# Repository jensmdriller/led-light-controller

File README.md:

# led-light-controller
This repo focuses around the development of an arduino based controller to program and control LED strip lights. 

- - - -

**Note**, I've created this repo to serve as a centralized storage for all of the LED project files. I'll update the README file as the project progresses. The README as well as the files contained within this folder should be a good reference for any future development. 

- - - -
### Overview
The components used herein are widely used in the hacker/maker community. Thus, much of the work has already been done for us. 
- For example, the **Atmel SAMD21** microcontroller is found in the Arduino Zero as well as many other developer boards.
- The lights are essentially a SMD 5050 LED with an integrated WS2811 microcontroller.
  - This integration of LED + MCU is referred to as **WS2812B**, but companies such as Adafruit use WS2812B LEDs and rebrand it as Neopixels. Other companies are starting to do the same. 
- The main hurdle of using WS2812B chips is their 5v operating voltage as well as their higher current draw. This prevents long runs without power injection along the way

- - - -

### Phase 1: Hardware Design
- Determining which microcontroller (MCU) and WiFi module to use
- Finalize schematic (including audio in or microphone)
- Configuring the power supplies
- Laying out the circuit board
- Ordering the circuit board and components
- Soldering/Assembling the first prototypes

### Phase 2: Coding - App & Embedded Software Design:
- Learn how the microcontroller (MCU) communicates with the LEDs
- Develop initial programs/sequences to control lights
- Work on WiFi integration
- App development (Android & IOS)
- Configure sync between app and LED controller via WiFI
- Refine app and implement additional functionality 

### Phase 3: Case/Enclosure Design
- Well let’s cross this bridge when we come to it

- - - -
- - - -

### Coming to Terms With Reality
- No one is going to buy this. This work is purely out of interest and enjoyment
- Good WiFi chipsets are protected by NDA. Thus we have to use more expensive and more discrete chipsets
- There already exists a lot of products on the market that have done exactly this - well almost...
- I'm pretty busy these days, so progress might be slow

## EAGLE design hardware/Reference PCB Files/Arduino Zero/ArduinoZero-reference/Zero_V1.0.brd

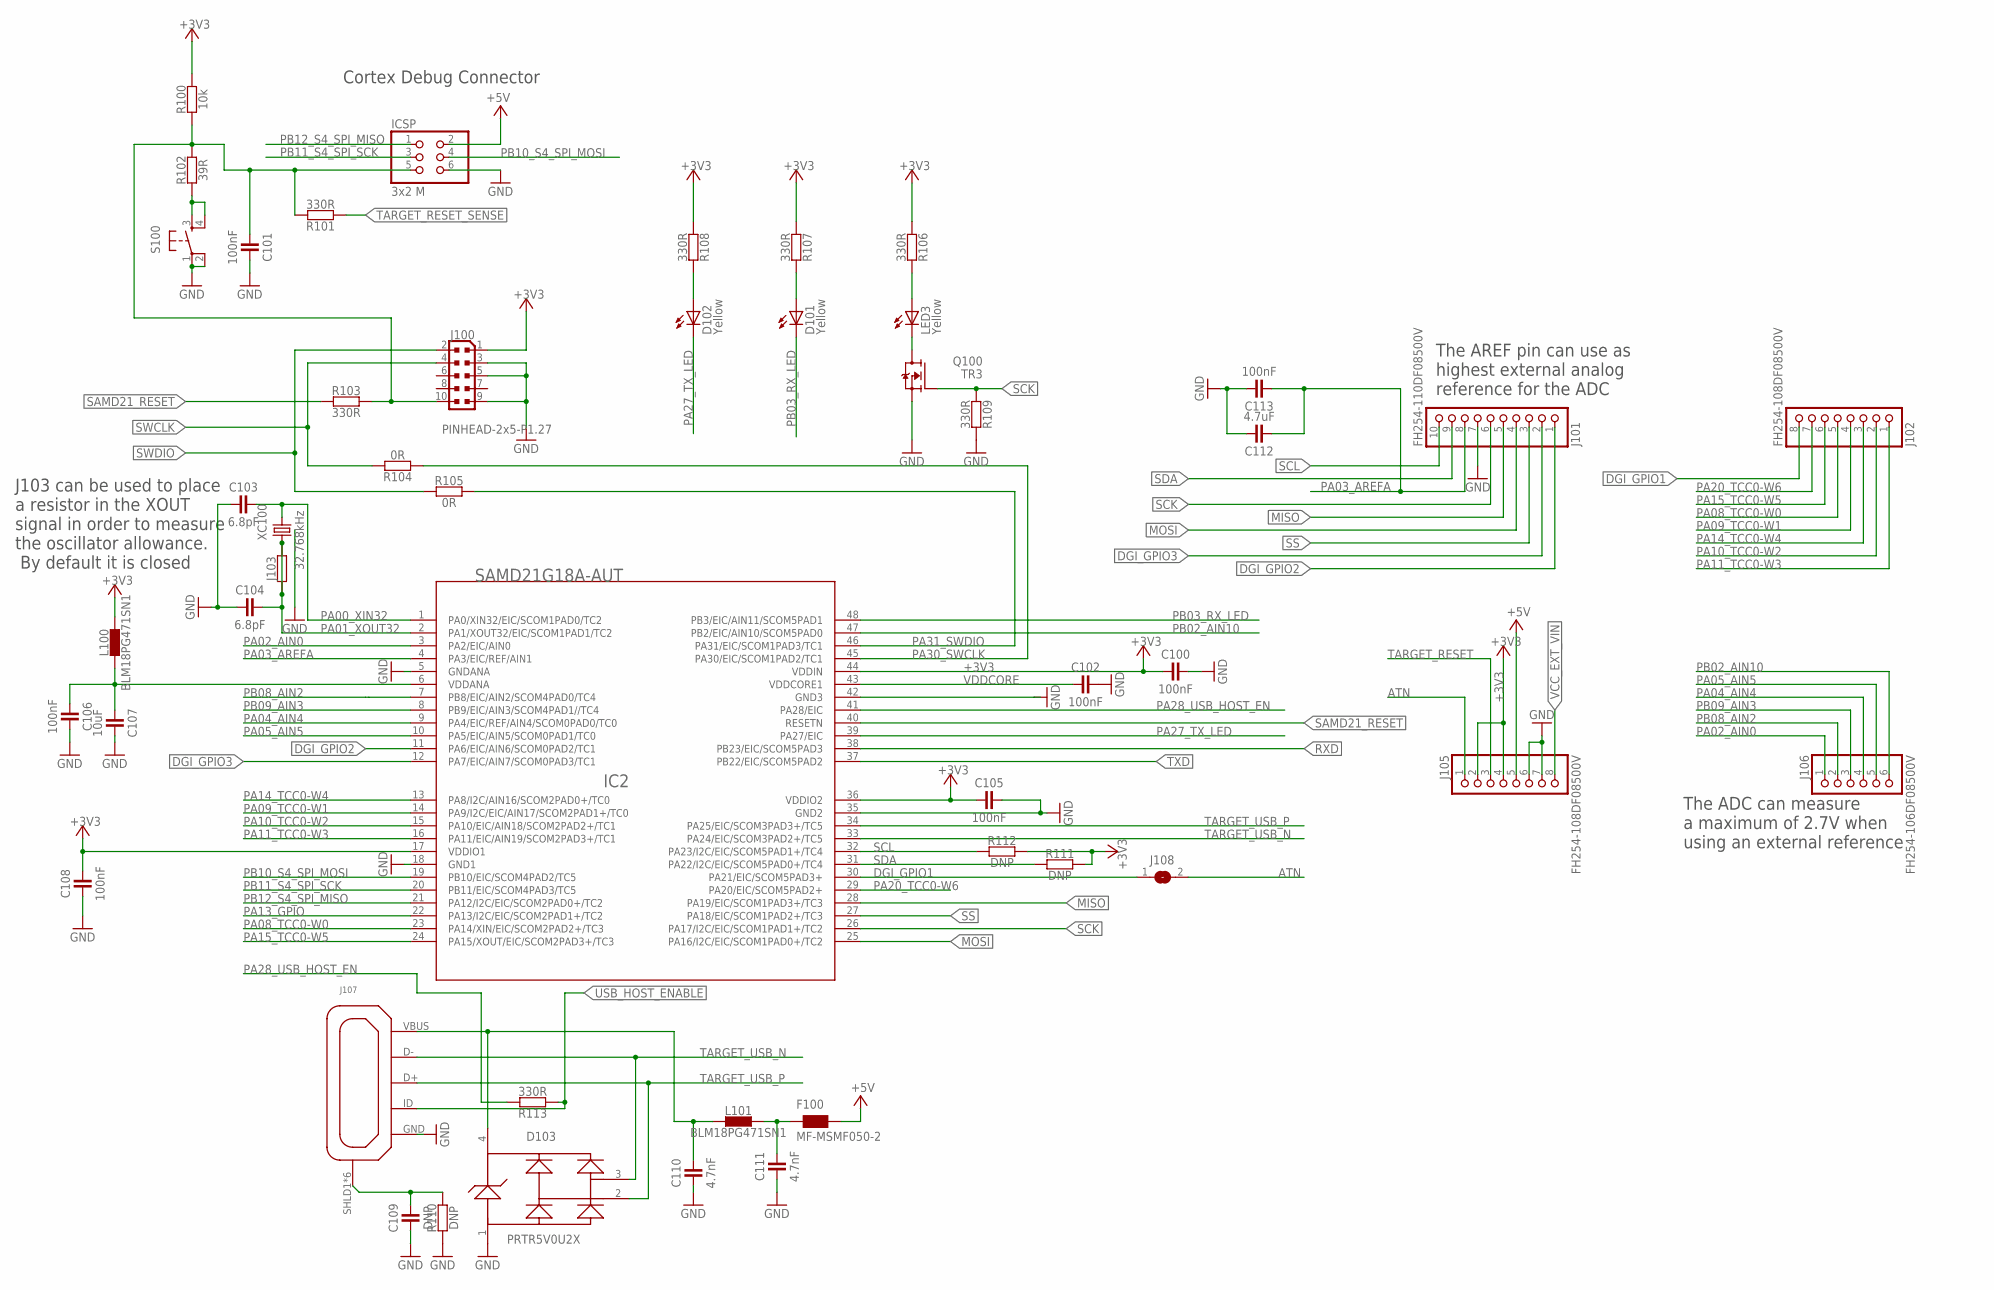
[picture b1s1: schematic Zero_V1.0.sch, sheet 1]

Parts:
C100, C101, C102, C105, C106, C108, C113: 100nF; C0402
C103, C104: 6.8pF; C0402
C107: 10uF; C0603
C109: DNP; C0402
C110, C111: 4.7nF; C0402
C112: 4.7uF; C0603
D101, D102: Yellow; CHIPLED_0805
D103: PRTR5V0U2XB; SOT143B
F100: MF-MSMF050-2; WUERTH-ELEKTRONIK_1812
IC2: SAMD21G18A-AUT; TQFP48
ICSP: 3x2 M; 2X03
J100: PINHEAD-2x5-P1.27; PINHEAD_2X05_127
J101: FH254-110DF08500V; 1X10
J102, J105: FH254-108DF08500V; 1X08
J103: RESISTORS-0402; C0402
J106: FH254-106DF08500V; 1X06
J107: ZX62-AB-5PA; USB-MICRO-10103594
J108: SJ
L100, L101: BLM18PG471SN1; C0603
LED3: Yellow; CHIPLED_0805
R100: 10k; C0402
R101, R103, R106, R107, R108, R109, R113: 330R; C0402
R102: 39R; C0402
R104, R105: 0R; C0402
R110, R111, R112: DNP; C0402
S100: PUSHBUTTON3; TS42_4PINS
TR3: Q100; SOT-23
XC100: 32.768kHz; CRYSTAL_TC26SMD

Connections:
+3V3: C100.1, C105.1, C108.2, IC2.17 (VDDIO1), IC2.36 (VDDIO2), IC2.44 (VDDIN), J100.1, J105.2, J105.4, L100.2, R100.2, R106.1, R107.1, R108.1, R111.2, R112.2; also elsewhere on the board
+5V: F100.2, ICSP.2, J105.5; also elsewhere on the board
ATN: J105.1, J108.2
DGI_GPIO1: IC2.30 (PA21/EIC/SCOM5PAD3+), J102.8, J108.1; also elsewhere on the board
DGI_GPIO2: IC2.11 (PA6/EIC/AIN6/SCOM0PAD2/TC1), J101.1; also elsewhere on the board
DGI_GPIO3: IC2.12 (PA7/EIC/AIN7/SCOM0PAD3/TC1), J101.2; also elsewhere on the board
GND: C100.2, C101.2, C102.2, C103.1, C104.1, C105.2, C106.2, C107.2, C108.1, C109.1, C110.1, C111.1, C112.2, C113.2, D103.1, IC2.5 (GNDANA), IC2.18 (GND1), IC2.35 (GND2), IC2.42 (GND3), ICSP.6, J100.3, J100.5, J100.9, J101.7, J105.6, J105.7, J107.GND, R109.2, R110.1, S100.1, S100.2, TR3.2 (S), XC100.P$1 (GND); also elsewhere on the board
MISO: IC2.28 (PA19/EIC/SCOM1PAD3+/TC3), J101.5; also elsewhere on the board
MOSI: IC2.25 (PA16/I2C/EIC/SCOM1PAD0+/TC2), J101.4; also elsewhere on the board
unnamed: LED3.C, TR3.1 (D)
unnamed: R102.1, S100.3, S100.4
unnamed: C110.2, D103.4, J107.VBUS (VUSB), L101.1
unnamed: C106.1, C107.1, IC2.6 (VDDANA), L100.1
unnamed: C109.2, J107.SHLD1 (SH), J107.SHLD2 (SH), J107.SHLD3 (SH), J107.SHLD4 (SH), J107.SHLD5 (SH), J107.SHLD6 (SH), R110.2
unnamed: C111.2, F100.1, L101.2
unnamed: D102.A, R108.2
unnamed: D101.A, R107.2
unnamed: LED3.A, R106.2
PA00_XIN32: C103.2, IC2.1 (PA0/XIN32/EIC/SCOM1PAD0/TC2), XC100.2
PA01_XOUT32: C104.2, IC2.2 (PA1/XOUT32/EIC/SCOM1PAD1/TC2), J103.1, J103.2, XC100.1
PA02_AIN0: IC2.3 (PA2/EIC/AIN0), J106.1
PA03_AREFA: C112.1, C113.1, IC2.4 (PA3/EIC/REF/AIN1), J101.8
PA04_AIN4: IC2.9 (PA4/EIC/REF/AIN4/SCOM0PAD0/TC0), J106.4
PA05_AIN5: IC2.10 (PA5/EIC/AIN5/SCOM0PAD1/TC0), J106.5
PA08_TCC0-W0: IC2.23 (PA14/XIN/EIC/SCOM2PAD2+/TC3), J102.5
PA09_TCC0-W1: IC2.14 (PA9/I2C/EIC/AIN17/SCOM2PAD1+/TC0), J102.4
PA10_TCC0-W2: IC2.15 (PA10/EIC/AIN18/SCOM2PAD2+/TC1), J102.2
PA11_TCC0-W3: IC2.16 (PA11/EIC/AIN19/SCOM2PAD3+/TC1), J102.1
PA13_GPIO: IC2.22 (PA13/I2C/EIC/SCOM2PAD1+/TC2)
PA14_TCC0-W4: IC2.13 (PA8/I2C/AIN16/SCOM2PAD0+/TC0), J102.3
PA15_TCC0-W5: IC2.24 (PA15/XOUT/EIC/SCOM2PAD3+/TC3), J102.6
PA20_TCC0-W6: IC2.29 (PA20/EIC/SCOM5PAD2+), J102.7
PA27_TX_LED: D102.C, IC2.39 (PA27/EIC)
PA28_USB_HOST_EN: IC2.41 (PA28/EIC), R113.2
PA30_SWCLK: IC2.45 (PA30/EIC/SCOM1PAD2/TC1), R104.1
PA31_SWDIO: IC2.46 (PA31/EIC/SCOM1PAD3/TC1), R105.2
PB02_AIN10: IC2.47 (PB2/EIC/AIN10/SCOM5PAD0), J106.6
PB03_RX_LED: D101.C, IC2.48 (PB3/EIC/AIN11/SCOM5PAD1)
PB08_AIN2: IC2.7 (PB8/EIC/AIN2/SCOM4PAD0/TC4), J106.2
PB09_AIN3: IC2.8 (PB9/EIC/AIN3/SCOM4PAD1//TC4), J106.3
PB10_S4_SPI_MOSI: IC2.19 (PB10/EIC/SCOM4PAD2/TC5), ICSP.4
PB11_S4_SPI_SCK: IC2.20 (PB11/EIC/SCOM4PAD3/TC5), ICSP.3
PB12_S4_SPI_MISO: IC2.21 (PA12/I2C/EIC/SCOM2PAD0+/TC2), ICSP.1
RXD: IC2.38 (PB23/EIC/SCOM5PAD3); also elsewhere on the board
SAMD21_RESET: IC2.40 (RESETN), R103.1; also elsewhere on the board
SCK: IC2.26 (PA17/I2C/EIC/SCOM1PAD1+/TC2), J101.6, R109.1, TR3.3 (G); also elsewhere on the board
SCL: IC2.32 (PA23/I2C/EIC/SCOM5PAD1+/TC4), J101.10, R112.1; also elsewhere on the board
SDA: IC2.31 (PA22/I2C/EIC/SCOM5PAD0+/TC4), J101.9, R111.1; also elsewhere on the board
SS: IC2.27 (PA18/EIC/SCOM1PAD2+/TC3), J101.3; also elsewhere on the board
SWCLK: J100.4, R104.2; also elsewhere on the board
SWDIO: J100.2, R105.1; also elsewhere on the board
TARGET_RESET: C101.1, ICSP.5, J100.10, J105.3, R100.1, R101.2, R102.2, R103.2
TARGET_RESET_SENSE: R101.1; also elsewhere on the board
TARGET_USB_N: D103.3, IC2.33 (PA24/EIC/SCOM3PAD2+/TC5), J107.D-
TARGET_USB_P: D103.2, IC2.34 (PA25/EIC/SCOM3PAD3+/TC5), J107.D+
TXD: IC2.37 (PB22/EIC/SCOM5PAD2); also elsewhere on the board
USB_HOST_ENABLE: J107.ID, R113.1; also elsewhere on the board
VCC_EXT_VIN: J105.8; also elsewhere on the board
VDDCORE: C102.1, IC2.43 (VDDCORE1)

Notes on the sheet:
Cortex Debug Connector
J103 can be used to place a resistor in the XOUT signal in order to measure the oscillator allowance. By default it is closed
The ADC can measure a maximum of 2.7V when using an external reference
The AREF pin can use as highest external analog reference for the ADC

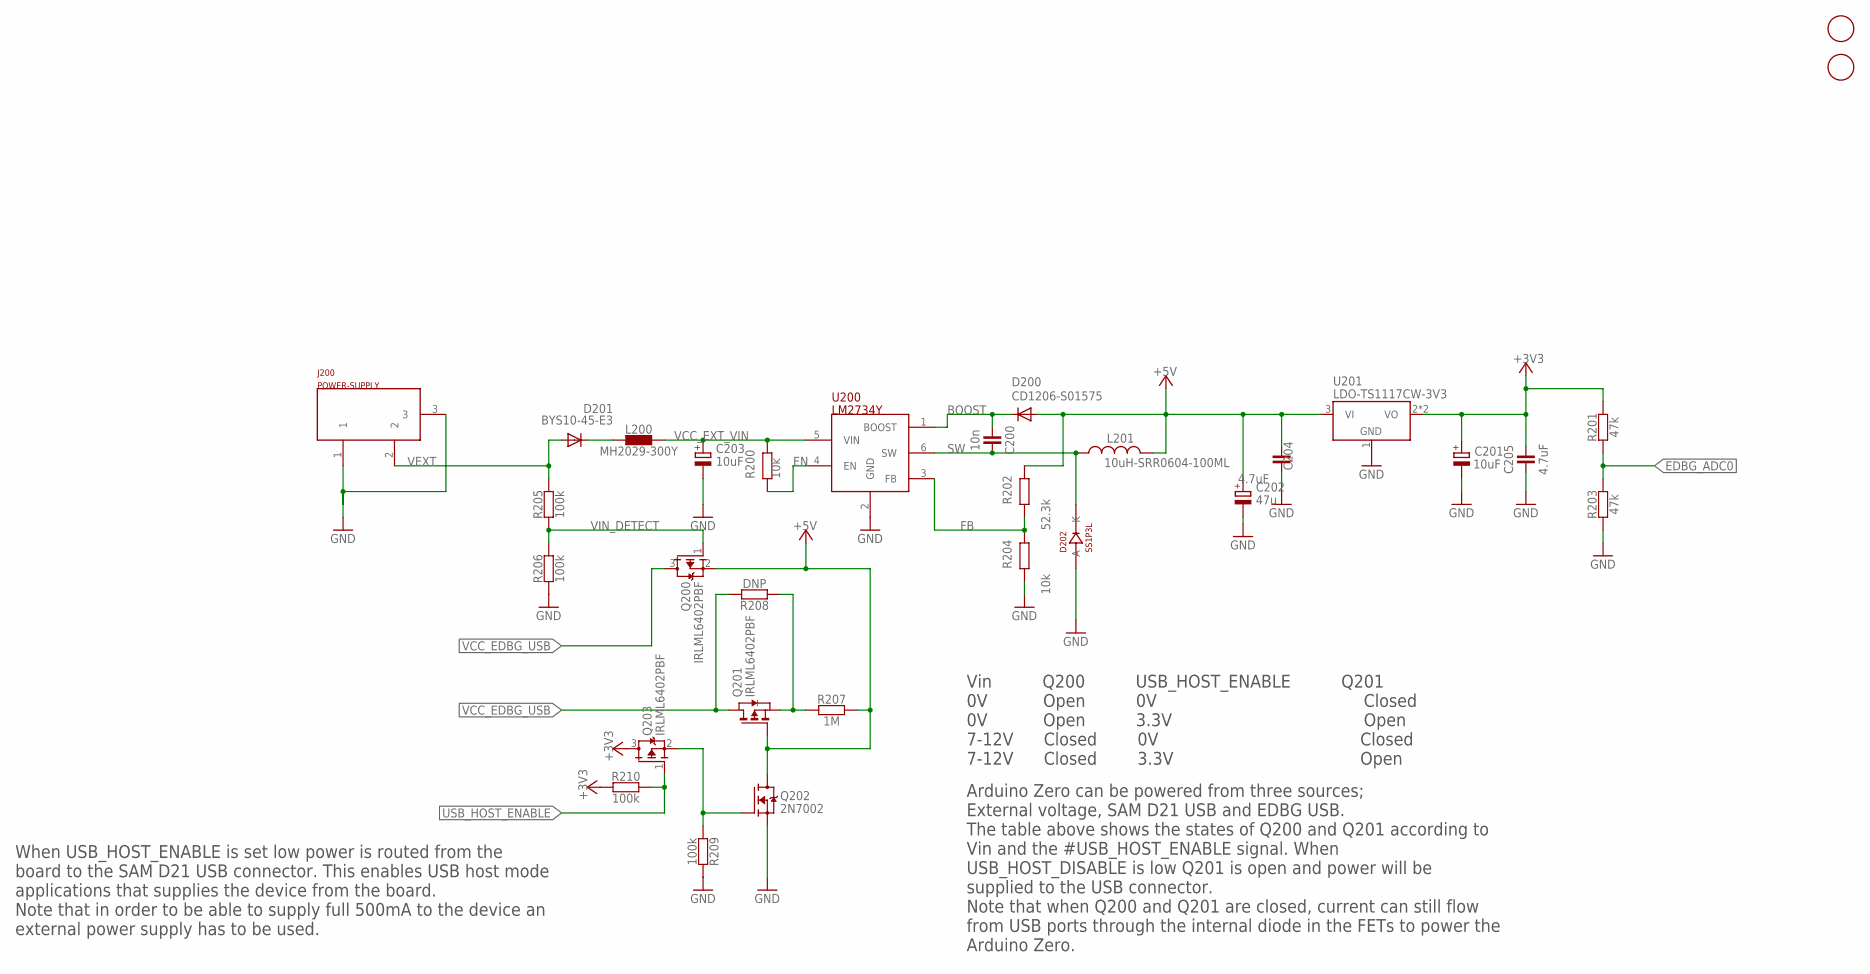
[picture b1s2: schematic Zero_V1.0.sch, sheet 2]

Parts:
C200: 10n; C0402
C201, C203: 10uF; PANASONIC_D
C202: 47u; PANASONIC_D
C204, C205: 4.7uF; C0603
D200: CD1206-S01575; MINIMELF
D201: BYS10-45-E3; MINIMELF
D202: SS1P3L; DO220AAL
FD1, FD2: FIDUCIALMOUNT; FIDUCIA-MOUNT
J200: POWER-SUPPLY; POWERSUPPLY_DC-21MM
L200: MH2029-300Y; C0805
L201: 10uH-SRR0604-100ML; SRR0604
Q200, Q203: IRLML6402PBF; SOT323
Q201: IRLML6402PBF; SOT-23
Q202: 2N7002; SOT23
R200, R204: 10k; C0402
R201, R203: 47k; C0402
R202: 52.3k; C0402
R205, R206, R209, R210: 100k; C0402
R207: 1M; C0402
R208: DNP; C0402
U200: LM2734Y; SOT23-6
U201: LDO-TS1117CW-3V3; SOT223

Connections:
+3V3: C201.+, C205.2, Q203.3 (D), R201.2, R210.1, U201.2 (VO), U201.4 (VO); also elsewhere on the board
+5V: C202.+, C204.1, D200.A, L201.P$2 (2), Q200.2 (S), Q201.3 (G), Q202.3 (D), R202.1, R207.2, U201.3 (VI); also elsewhere on the board
BOOST: C200.1, D200.C, U200.1 (BOOST)
EDBG_ADC0: R201.1, R203.2; also elsewhere on the board
EN: R200.2, U200.4 (EN)
FB: R202.2, R204.1, U200.3 (FB)
GND: C201.-, C202.-, C203.-, C204.2, C205.1, D202.P$2 (A), J200.1, J200.3, Q202.2 (S), R203.1, R204.2, R206.1, R209.2, U200.2 (GND), U201.1 (GND); also elsewhere on the board
unnamed: Q201.2 (S), R207.1, R208.1
unnamed: D201.C, L200.1
unnamed: Q202.1 (G), Q203.2 (S), R209.1
SW: C200.2, D202.P$1 (K), L201.P$1 (1), U200.6 (SW)
USB_HOST_ENABLE: Q203.1 (G), R210.2; also elsewhere on the board
VCC_EDBG_USB: Q200.3 (D), Q201.1 (D), R208.2; also elsewhere on the board
VCC_EXT_VIN: C203.+, L200.2, R200.1, U200.5 (VIN); also elsewhere on the board
VEXT: D201.A, J200.2, R205.2
VIN_DETECT: Q200.1 (G), R205.1, R206.2

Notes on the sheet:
Arduino Zero can be powered from three sources; External voltage, SAM D21 USB and EDBG USB. The table above shows the states of Q200 and Q201 according to Vin and the #USB_HOST_ENABLE signal. When USB_HOST_DISABLE is low Q201 is open and power will be supplied to the USB connector. Note that when Q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
Vin Q200 USB_HOST_ENABLE Q201 0V Open 0V Closed 0V Open 3.3V Open 7-12V Closed 0V Closed 7-12V Closed 3.3V Open
When USB_HOST_ENABLE is set low power is routed from the board to the SAM D21 USB connector. This enables USB host mode applications that supplies the device from the board. Note that in order to be able to supply full 500mA to the device an external power supply has to be used.

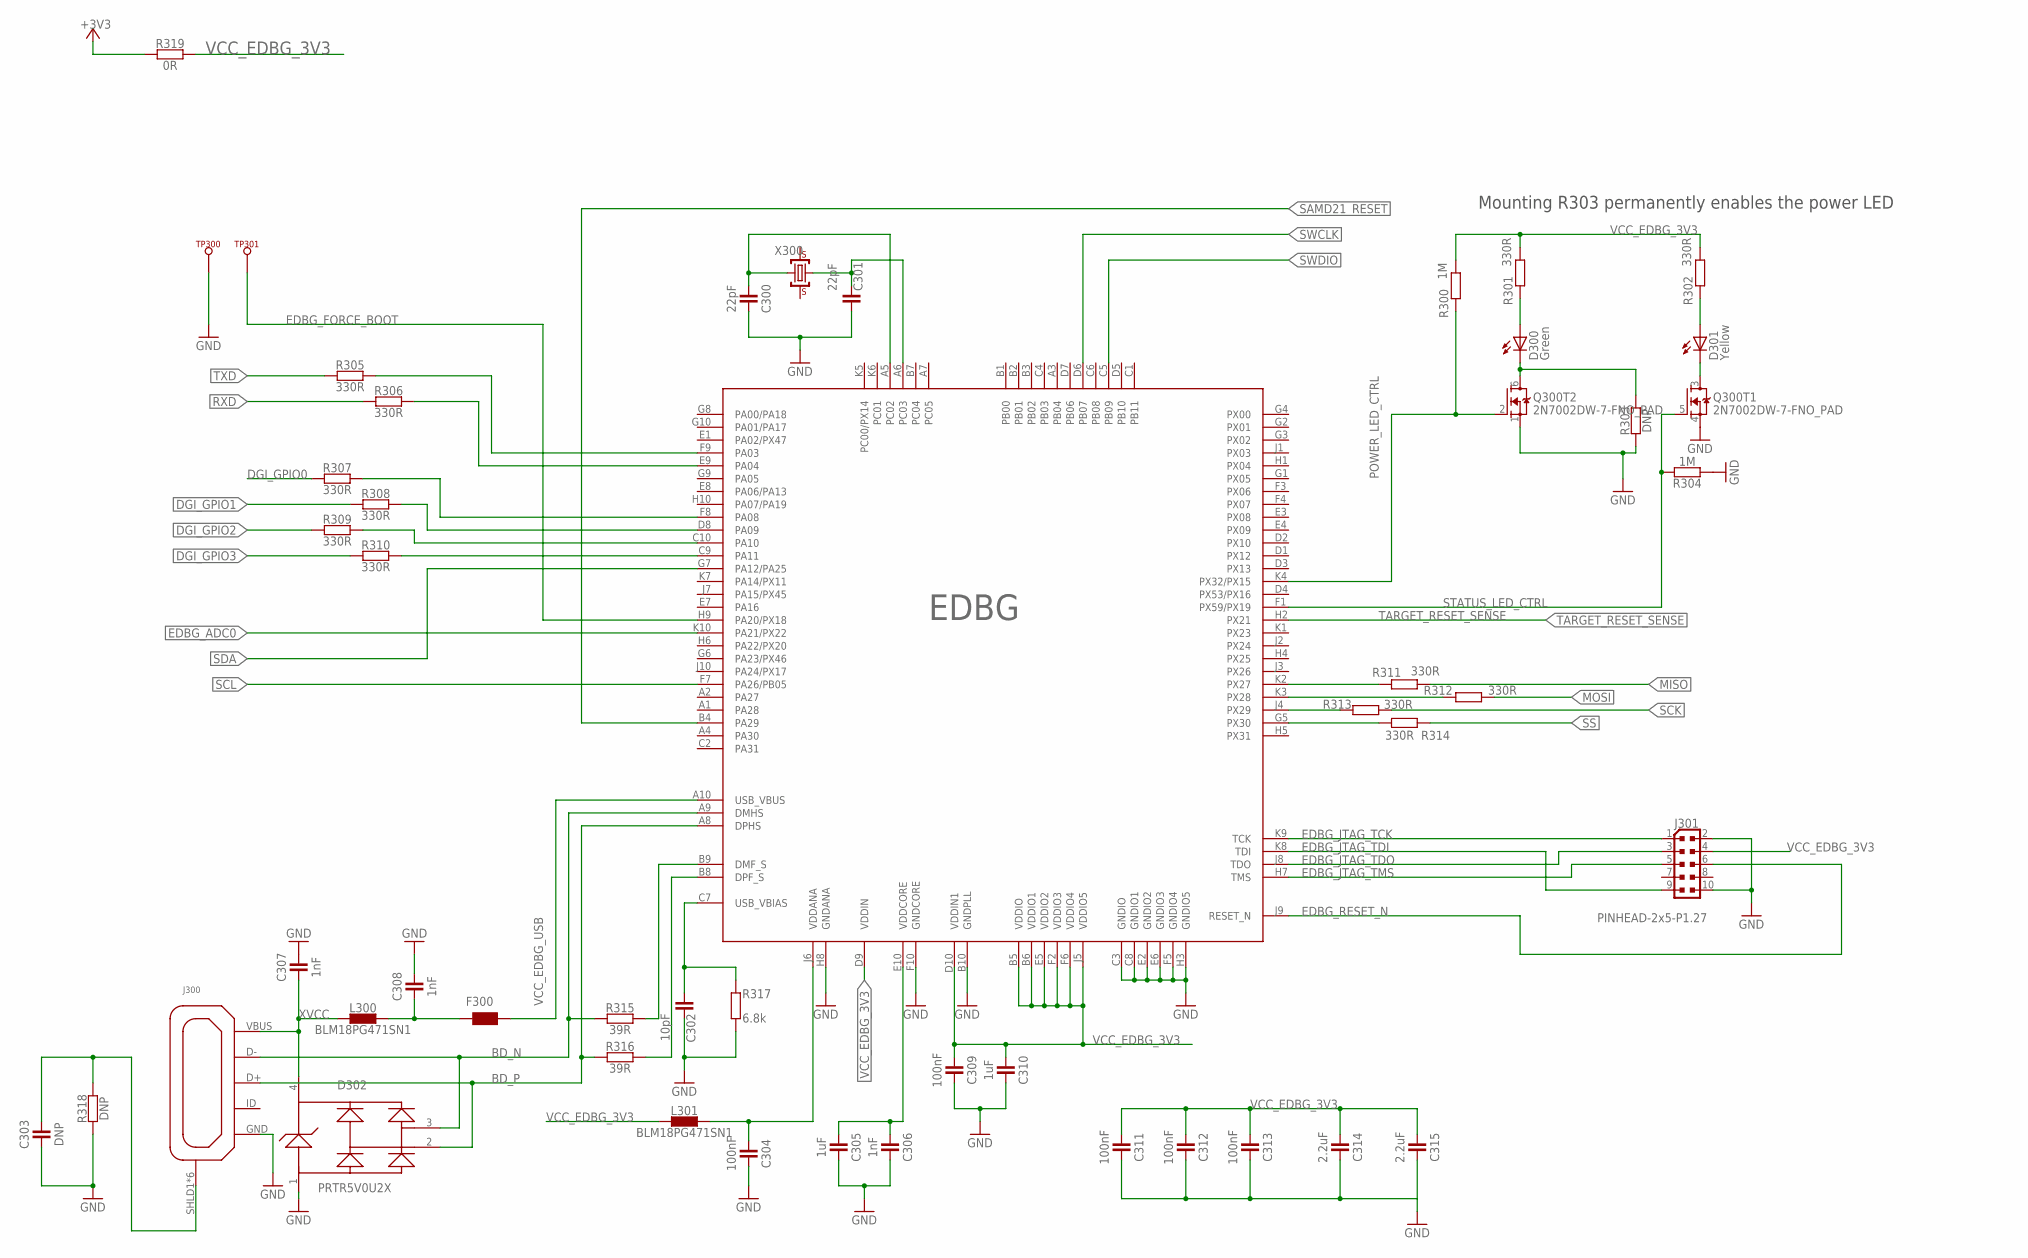
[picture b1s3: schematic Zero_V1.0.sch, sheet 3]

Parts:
C300, C301: 22pF; C0402
C302: 10pF; C0402
C303: DNP; C0402
C304, C309, C311, C312, C313: 100nF; C0402
C305, C310: 1uF; C0402
C306, C307, C308: 1nF; C0402
C314, C315: 2.2uF; C0402
D300: Green; CHIPLED_0805
D301: Yellow; CHIPLED_0805
D302: PRTR5V0U2XB; SOT143B
EDBG: EDBG; VFBGA100
F300: WUERTH-ELEKTRONIK_WE-CBF_1812; WUERTH-ELEKTRONIK_1812
J300: ZX62-AB-5PA; USB-MICRO-10103594
J301: PINHEAD-2x5-P1.27; PINHEAD_2X05_127
L300, L301: BLM18PG471SN1; C0603
Q300: 2N7002DW-7-FNO_PAD; PWR_SC70-6L2
R300, R304: 1M; C0402
R301, R302, R305, R306, R307, R308, R309, R310, R311, R312, R313, R314: 330R; C0402
R303, R318: DNP; C0402
R315, R316: 39R; C0402
R317: 6.8k; C0402
R319: 0R; C0402
TP300, TP301: TP_SP; TP-SP
X300: 12mHz-12pF-K7; CRYSTAL-5.4-3.2

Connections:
+3V3: R319.1; also elsewhere on the board
BD_N: D302.3, EDBG.A9 (DMHS), J300.D-, R315.1
BD_P: D302.2, EDBG.A8 (DPHS), J300.D+, R316.1
DGI_GPIO0: R307.1
DGI_GPIO1: R308.1; also elsewhere on the board
DGI_GPIO2: R309.1; also elsewhere on the board
DGI_GPIO3: R310.1; also elsewhere on the board
EDBG_ADC0: EDBG.K10 (PA21/PX22); also elsewhere on the board
EDBG_FORCE_BOOT: EDBG.H9 (PA20/PX18), TP301.X
EDBG_JTAG_TCK: EDBG.K9 (TCK), J301.1
EDBG_JTAG_TDI: EDBG.K8 (TDI), J301.9
EDBG_JTAG_TDO: EDBG.J8 (TDO), J301.3
EDBG_JTAG_TMS: EDBG.H7 (TMS), J301.5
EDBG_RESET_N: EDBG.J9 (RESET_N), J301.6
GND: C300.2, C301.2, C302.2, C303.1, C304.2, C305.2, C306.2, C307.2, C308.2, C309.2, C310.2, C311.2, C312.2, C313.2, C314.2, C315.2, D302.1, EDBG.B10 (GNDPLL), EDBG.C3 (GNDIO), EDBG.C8 (GNDIO1), EDBG.E2 (GNDIO2), EDBG.E6 (GNDIO3), EDBG.F5 (GNDIO4), EDBG.F10 (GNDCORE), EDBG.H3 (GNDIO5), EDBG.H8 (GNDANA), J300.GND, J301.2, J301.10, Q300.1 (S), Q300.4 (S), R303.1, R304.1, R317.1, R318.1, TP300.X; also elsewhere on the board
MISO: R311.2; also elsewhere on the board
MOSI: R312.2; also elsewhere on the board
unnamed: D300.C, Q300.6 (D), R303.2
unnamed: D301.C, Q300.3 (D)
unnamed: C303.2, J300.SHLD1 (SH), J300.SHLD2 (SH), J300.SHLD3 (SH), J300.SHLD4 (SH), J300.SHLD5 (SH), J300.SHLD6 (SH), R318.2
unnamed: C308.1, F300.1, L300.2
unnamed: EDBG.B9 (DMF_S), R315.2
unnamed: EDBG.B8 (DPF_S), R316.2
unnamed: C302.1, EDBG.C7 (USB_VBIAS), R317.2
unnamed: C301.1, EDBG.A6 (PC03), X300.1 (C1)
unnamed: C300.1, EDBG.A5 (PC02), X300.3 (C2)
unnamed: C305.1, C306.1, EDBG.E10 (VDDCORE)
unnamed: C304.1, EDBG.J6 (VDDANA), L301.2
unnamed: EDBG.K2 (PX27), R311.1
unnamed: EDBG.K3 (PX28), R312.1
unnamed: EDBG.J4 (PX29), R313.1
unnamed: EDBG.G5 (PX30), R314.1
unnamed: EDBG.C9 (PA11), R310.2
unnamed: EDBG.C10 (PA10), R309.2
unnamed: EDBG.D8 (PA09), R308.2
unnamed: EDBG.F8 (PA08), R307.2
unnamed: EDBG.E9 (PA04), R306.2
unnamed: EDBG.F9 (PA03), R305.2
unnamed: D300.A, R301.1
unnamed: D301.A, R302.1
POWER_LED_CTRL: EDBG.K4 (PX32/PX15), Q300.2 (G), R300.1
RXD: R306.1; also elsewhere on the board
SAMD21_RESET: EDBG.B4 (PA29); also elsewhere on the board
SCK: R313.2; also elsewhere on the board
SCL: EDBG.F7 (PA26/PB05); also elsewhere on the board
SDA: EDBG.G7 (PA12/PA25); also elsewhere on the board
SS: R314.2; also elsewhere on the board
STATUS_LED_CTRL: EDBG.F1 (PX59/PX19), Q300.5 (G), R304.2
SWCLK: EDBG.D6 (PB07); also elsewhere on the board
SWDIO: EDBG.C5 (PB09); also elsewhere on the board
TARGET_RESET_SENSE: EDBG.H2 (PX21); also elsewhere on the board
TXD: R305.1; also elsewhere on the board
VCC_EDBG_3V3: C309.1, C310.1, C311.1, C312.1, C313.1, C314.1, C315.1, EDBG.B5 (VDDIO), EDBG.B6 (VDDIO1), EDBG.D9 (VDDIN), EDBG.D10 (VDDIN1), EDBG.E5 (VDDIO2), EDBG.F2 (VDDIO3), EDBG.F6 (VDDIO4), EDBG.J5 (VDDIO5), J301.4, L301.1, R300.2, R301.2, R302.2, R319.2
VCC_EDBG_USB: EDBG.A10 (USB_VBUS), F300.2; also elsewhere on the board
XVCC: C307.1, D302.4, J300.VBUS (VUSB), L300.1

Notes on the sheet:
Mounting R303 permanently enables the power LED

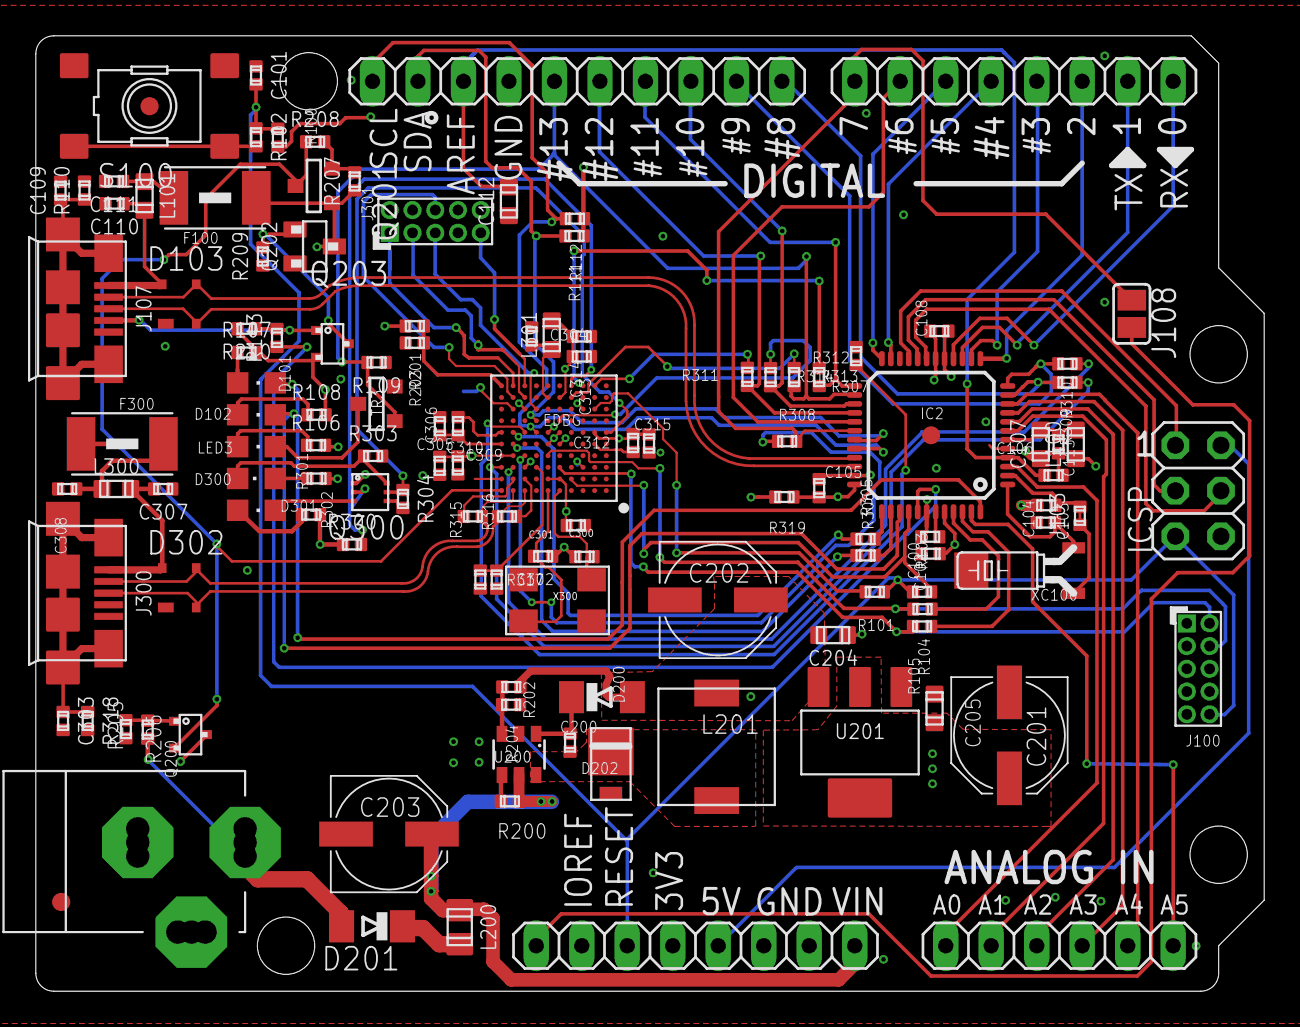
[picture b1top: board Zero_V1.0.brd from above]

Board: 4 copper layers, 68.6 x 53.3 mm, 128 parts (0 on the bottom side), 104 nets.

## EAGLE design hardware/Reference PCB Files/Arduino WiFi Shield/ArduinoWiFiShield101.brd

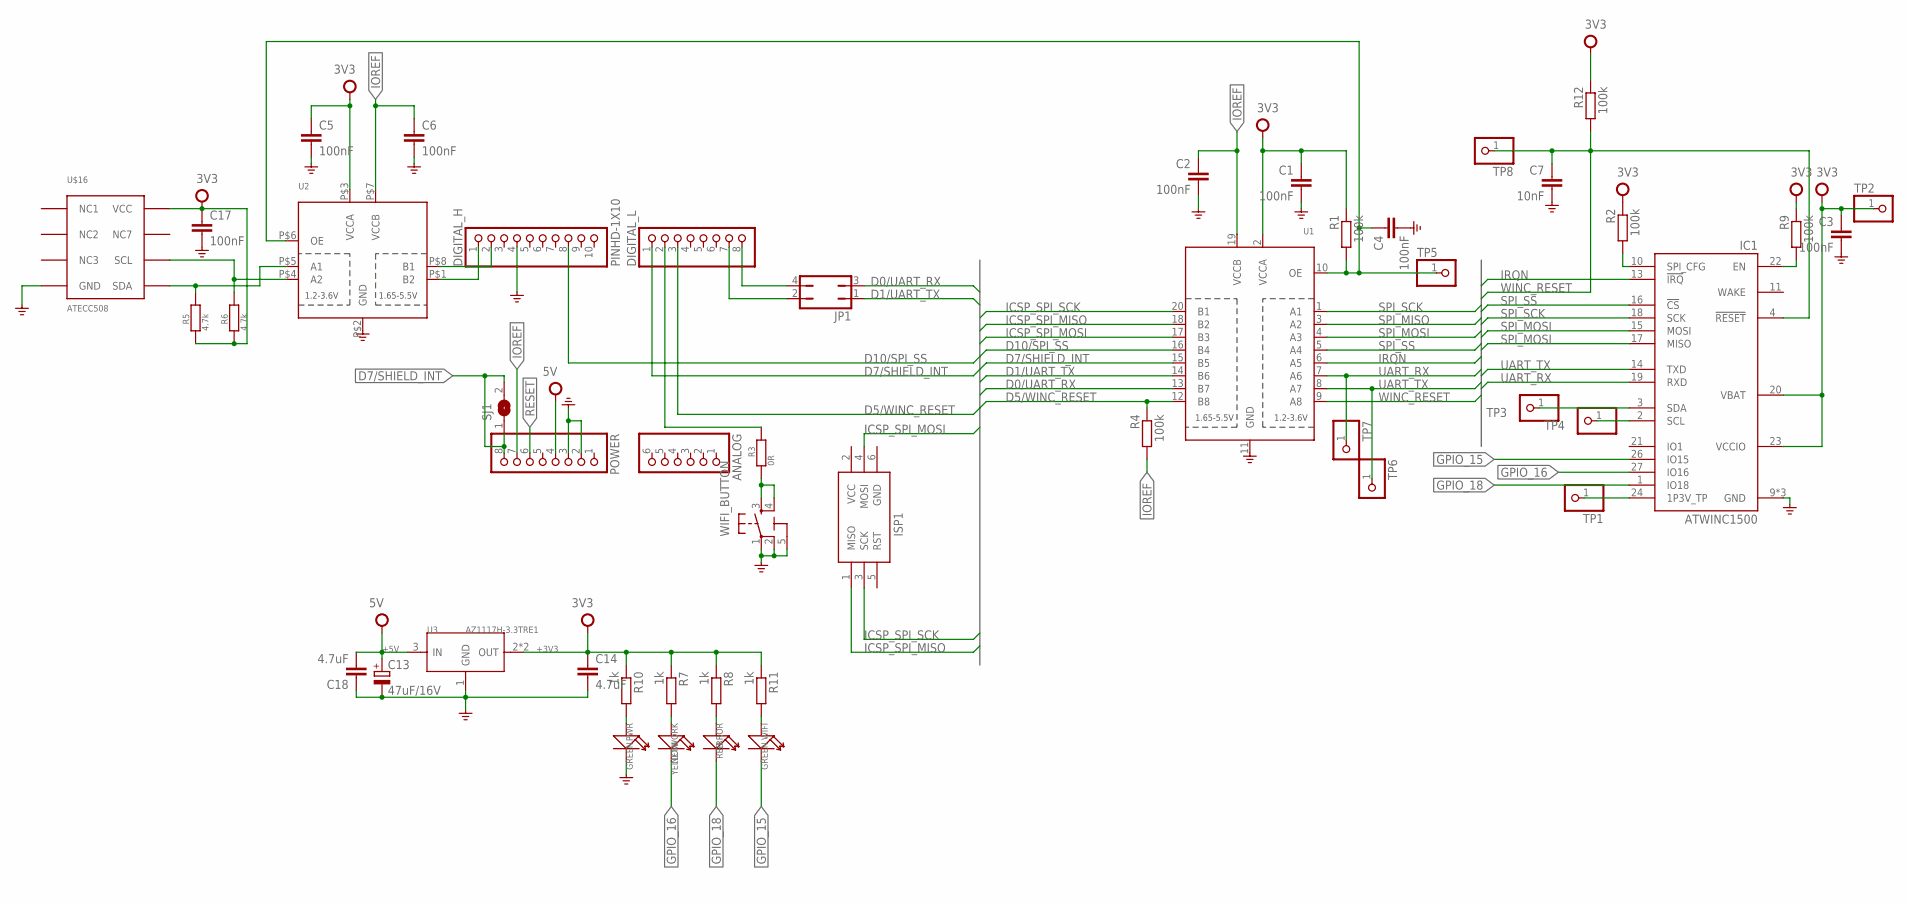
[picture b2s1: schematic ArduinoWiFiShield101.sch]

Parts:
ANALOG: PINHD-1X6B; 1X06-BIG
C1, C2, C3, C4, C5, C6, C17: 100nF; C0402
C7: 10nF; C0402
C13: 47uF/16V; 140CLH-0810
C14, C18: 4.7uF; C0603
DIGITAL_H: PINHD-1X10; 1X10-BIG
DIGITAL_L: PINHD-1X8BIG; 1X08-BIG
ERROR: RED; LED-0603
IC1: ATWINC1500; ATWINC1500-MR210
ISP1: AVRISP-6; AVRISP
JP1: JP2Q
NETWORK: YELLOW; LED-0603
POWER: PINHD-1X8BIG; 1X08-BIG
PWR: GREEN; LED-0603
R1, R2, R4, R9, R12: 100k; R0402
R3: 0R; R0402
R5, R6: 4.7k; R0402
R7, R8, R10, R11: 1k; R0402
SJ1: SJ
TP1, TP2, TP3, TP4, TP5, TP6, TP7, TP8: PINHD-1X1_2.00; 1X01M
U1: TXB0108PWR; TSSOP20
U2: TXS0102; VFSOP-8
U3: AZ1117H-3.3TRE1; SOT-223
U$16: ATECC508; DFN-8.3X3.PAD
WIFI: GREEN; LED-0603
WIFI_BUTTON: TS42

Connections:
3V3: ISP1.2 (VCC)
+3V3: C1.1, C3.1, C5.1, C14.1, C17.1, IC1.20 (VBAT), IC1.23 (VCCIO), R1.1, R2.1, R5.1, R6.1, R7.1, R8.1, R9.1, R10.1, R11.1, R12.1, TP2.1, U1.2 (VCCA), U3.2 (OUT), U3.TER (OUT), U$16.8 (VCC)
+5V: C13.+, C18.2, POWER.4, U3.3 (IN)
D0/UART_RX: JP1.3, U1.13 (B7)
D1/UART_TX: JP1.1, U1.14 (B6)
D5/WINC_RESET: DIGITAL_L.3, R4.1, U1.12 (B8)
D7/SHIELD_INT: DIGITAL_L.1, POWER.8, SJ1.1, SJ1.2, U1.15 (B5)
D10/SPI_SS: DIGITAL_H.8, U1.16 (B4)
GND: C1.2, C2.2, C3.2, C4.2, C5.2, C6.2, C7.2, C13.-, C14.2, C17.2, C18.1, DIGITAL_H.4, IC1.9 (GND), IC1.12 (GND), IC1.28 (GND), ISP1.6 (GND), POWER.2, POWER.3, PWR.-, U1.11 (GND), U2.P$2 (GND), U3.1 (GND), U$16.4 (GND), U$16.PAD (GND), WIFI_BUTTON.1, WIFI_BUTTON.2, WIFI_BUTTON.5 (5-GND)
GPIO_15: IC1.26 (IO15), WIFI.-
GPIO_16: IC1.27 (IO16), NETWORK.-
GPIO_18: ERROR.-, IC1.1 (IO18)
ICSP_SPI_MISO: ISP1.1 (MISO), U1.18 (B2)
ICSP_SPI_MOSI: ISP1.4 (MOSI), U1.17 (B3)
ICSP_SPI_SCK: ISP1.3 (SCK), U1.20 (B1)
IOREF: C2.1, C6.1, POWER.7, R4.2, U1.19 (VCCB)
IRQN: IC1.13 (!IRQ), U1.6 (A5)
unnamed: NETWORK.+, R7.2
unnamed: DIGITAL_L.2, R3.1
unnamed: DIGITAL_L.8, JP1.4
unnamed: ERROR.+, R8.2
unnamed: R11.2, WIFI.+
unnamed: DIGITAL_L.7, JP1.2
unnamed: C4.1, R1.2, TP5.1, U1.10 (OE), U2.P$6 (OE)
unnamed: IC1.10 (SPI_CFG), R2.2
unnamed: IC1.22 (EN), R9.2
unnamed: DIGITAL_H.1, U2.P$1 (B2)
unnamed: R5.2, U2.P$5 (A1), U$16.5 (SDA)
unnamed: IC1.24 (1P3V_TP), TP1.1
unnamed: IC1.3 (SDA), TP3.1
unnamed: IC1.2 (SCL), TP4.1
unnamed: R3.2, WIFI_BUTTON.3, WIFI_BUTTON.4
unnamed: PWR.+, R10.2
RESET: POWER.6
SCL: R6.2, U2.P$4 (A2), U$16.6 (SCL)
SDA: DIGITAL_H.2, U2.P$8 (B1)
SPI_MISO: IC1.17 (MISO), U1.3 (A2)
SPI_MOSI: IC1.15 (MOSI), U1.4 (A3)
SPI_SCK: IC1.18 (SCK), U1.1 (A1)
SPI_SS: IC1.16 (!CS), U1.5 (A4)
UART_RX: IC1.19 (RXD), TP7.1, U1.7 (A6)
UART_TX: IC1.14 (TXD), TP6.1, U1.8 (A7)
WINC_RESET: C7.1, IC1.4 (!RESET), R12.2, TP8.1, U1.9 (A8)

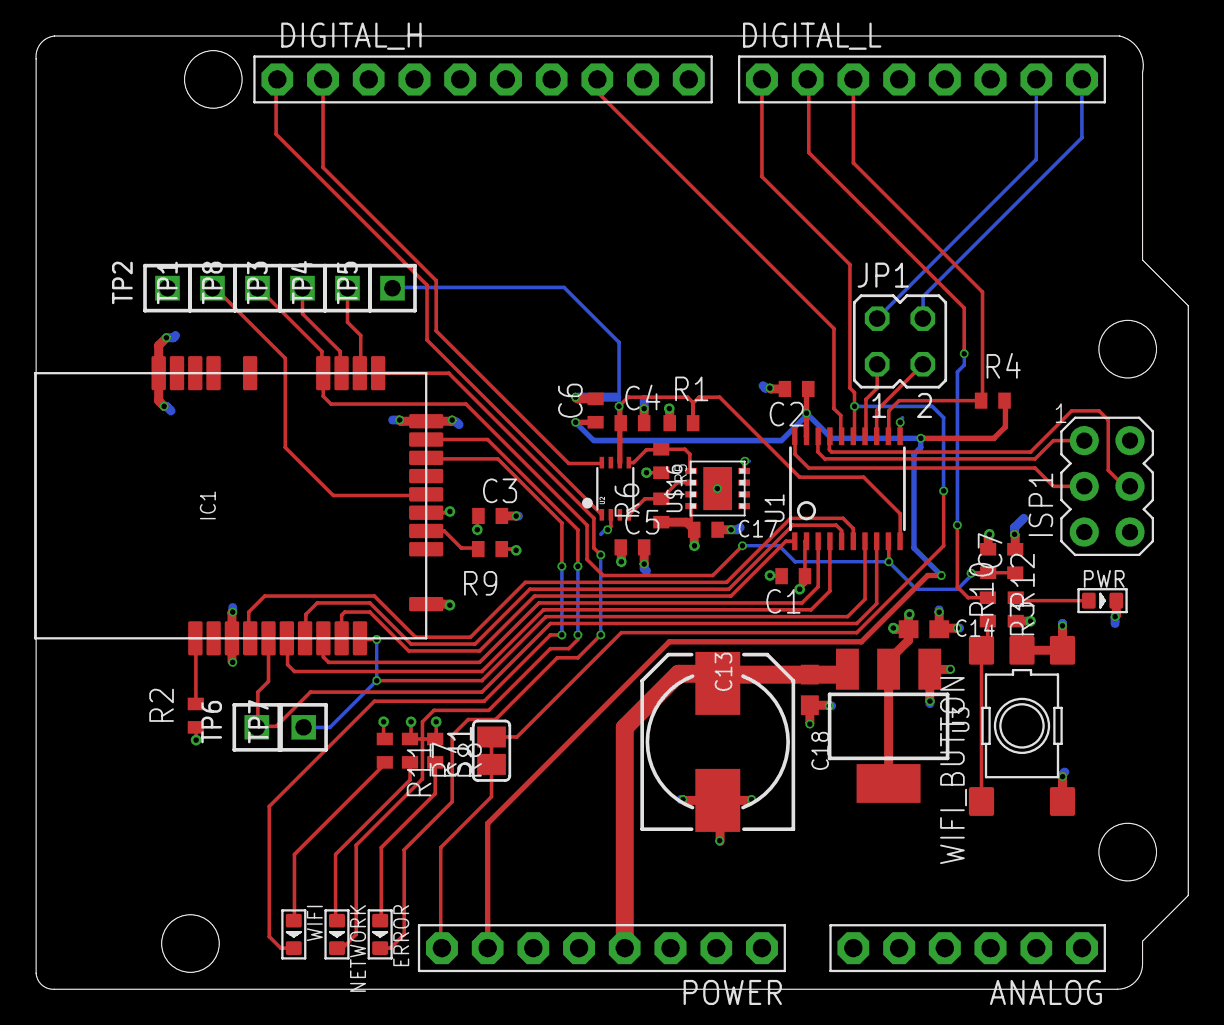
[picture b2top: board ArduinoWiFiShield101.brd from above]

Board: 4 copper layers, 64.0 x 53.0 mm, 48 parts (0 on the bottom side), 41 nets.

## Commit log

2018-01-12 initializing led-project repo
2018-01-13 added log to repo
2018-01-13 updated main repo README
2018-01-13 Incorrect extension for readme file
2018-01-13 adding hardware files to repo
2018-01-13 adding software files to repo
2018-01-13 Added note indicating that code is from FastLED repo, not my own
